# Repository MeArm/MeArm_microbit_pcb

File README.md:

## MeArm micro:bit Control Board PCB

<a href="https://shop.mearm.com/products/mearm-controller-board-for-micro-bit"><br/>
Click here to purchase one from the MeArm shop</a>

PCB files for the MeArm micro:bit Control Board PCB. Format is KiCad schematic and board layout
* https://shop.mearm.com/products/mearm-controller-board-for-micro-bit

### Description

This handy control board breaks uses pins P13, P14, P15, and P16 for controlling servo motors to manipulate a 4 axis robot arm. Pins P0, P1, P2, and P3 are used for analog inputs.

Disabling the LED matrix using the [following code](https://makecode.microbit.org/_8JDe2RcyMcPF) allows us to gain this extra functionality, and also times out the servo motors when they are not in use.

6V power can be supplied through a centre positive 2.1mm barrel jack. USB power is available but not advised if you're planning on moving quickly. 

### License

MeArm Robotics invests time and resources providing this open source design, please support MeArm Robotics and open-source hardware by purchasing products from [MeArm](https://www.mearm.com)!

Designed by Benjamin Gray/phenoptix for MeArm Robotics.

Creative Commons Attribution/Share-Alike, all text above must be included in any redistribution. See license.txt for additional details.

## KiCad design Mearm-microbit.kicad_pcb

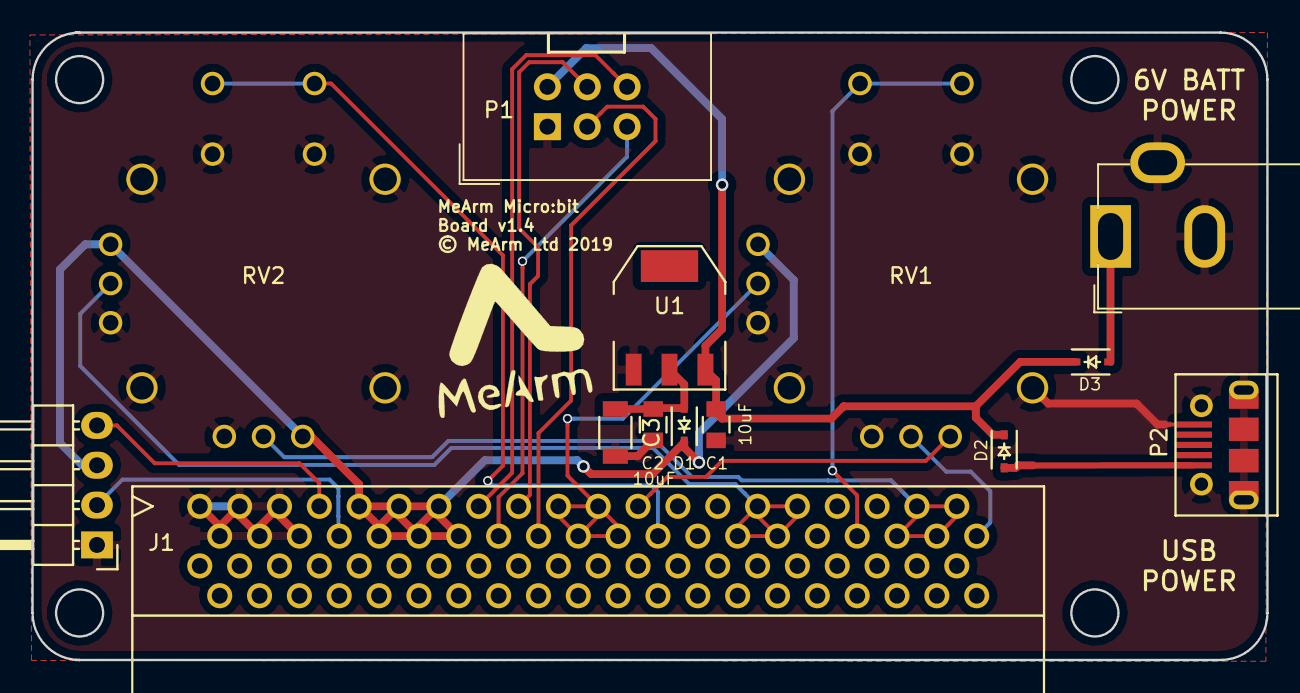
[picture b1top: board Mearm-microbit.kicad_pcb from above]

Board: 2 copper layers, 78.7 x 40.0 mm, 13 parts (0 on the bottom side), 18 nets.

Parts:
C1, C2: 10uF; C_0805
C3: 100uF; C_1206
D1, D2, D3: BAT60AE6327; SOD-323
J1: microbit_edge_connector; Microbit_Connector_RA_TH
P1: CONN_02X03; IDC-Header_2x03_Pitch2.54mm_Straight
P2: USB_OTG; MOLEX_MICRO_USB
P4: CONN_01X04; Pin_Header_Angled_1x04
RV1, RV2: DUAL_POT_JOYSTICK; JOYSTICK
U1: LD1117S33CTR; SOT-223

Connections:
+3V3: D1.1, J1.17, J1.19, J1.21, J1.23, J1.25, J1.27, P4.3, RV1.6, RV2.1, RV2.6
+5V: C1.1, D2.1, D3.1, P1.2, U1.3
BASE_JOYSTICK: J1.71, J1.73, J1.75, J1.77, RV2.2
BASE_SERVO: J1.35, P1.3
BUTTON_A: J1.67, RV1.8
BUTTON_B: J1.47, RV2.8
GND: C1.2, C2.2, C3.2, J1.1, J1.3, J1.5, J1.7, J1.9, J1.11, P1.1, P2.5, P2.6, P4.1, RV1.3, RV1.4, RV1.7, RV1.9, RV2.3, RV2.4, RV2.7, RV2.9, U1.1
GRIP_JOYSTICK: J1.79, RV1.2
GRIP_JOY_ENABLE: J1.45, RV1.1
GRIP_SERVO: J1.29, P1.6
LEFT_JOYSTICK: J1.37, J1.39, J1.41, J1.43, RV1.5
LEFT_SERVO: J1.33, P1.4
unnamed: C2.1, C3.1, D1.2, U1.2
unnamed: D2.2, P2.1
RIGHT_JOYSTICK: J1.55, J1.57, J1.59, J1.61, RV2.5
RIGHT_SERVO: J1.31, P1.5
SCL: J1.15, P4.2
SDA: J1.13, P4.4

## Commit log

2023-04-27 pcb assets and readme
2023-04-27 cough cough MeArm not Adafruit

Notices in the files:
Mearm-microbit.kicad_pcb:
© MeArm Ltd 2019
